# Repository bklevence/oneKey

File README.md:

oneKey 2020
===========

Project Focus
-------------------
Developing a low-cost (<$2) and accessible derivative of the MaKey MaKey so that it can be sustainably deployed via workshops at various library branches.

The aim is to introduce youth in underserved/low-income communities to making hardware that they can then tinker/play/make with. It's adressing the question "Can I take this home?" and the inability for youth to use take projects using digital media tools such as the MaKey MaKey home.

In participating in this process we hope for them to take more ownership of their tools. We're also trying to adress wether or not the library and its participants can make their own tools for learning via desktop manufacturing and production methods.

So what is a MaKey MaKey?
-------------------
From Sparkfun's [*MaKey MaKey Documentation*](https://github.com/sparkfun/makeymakey):

*"Using the MaKey MaKey you can make anything into a key (get it?) just by connecting a few alligator clips. The MaKey MaKey is an invention kit that tricks your computer into thinking that almost anything is a keyboard. This allows you to hook up all kinds of fun things as an input."*

**How does it work?**

*"The MaKey MaKey uses high resistance switching to detect when you've made a connection even through materials that aren't very conductive (like leaves, pasta or people). This technique attracts noise on the input, so a moving window averager is used to lowpass the noise. The on-board ATMega32u4 communicates with your computer using the Human Interface Device (HID) protocol which means that it can act like a keyboard or mouse."*

Methods
-------------------
The original oneKey uses a vinyl cutter and 3M copper tape to make a low-barrier and low-cost method for creating traces to solder onto. If working indoors take precautions with ventilalation etc. Working currently on a PCB kit version.

Need for the oneKey
-------------------
* 3M Copper Tape (used to be much cheaper, working on a thinner tape iteration.) ([Buy](http://www.amazon.com/inch-yds-Copper-Foil-Tape/dp/B00CBPM9RY/ref=sr_1_2?ie=UTF8&qid=1429671129&sr=8-2&keywords=copper+tape+3%22) | [HowTo](http://www.kobakant.at/DIY/?p=1132))
* Attiny85 ([Buy](http://www.digikey.com/product-detail/en/0/ATTINY85-20PU-ND) | [HowTo](about:blank))
* Attiny85 Standoff/ IC DIP Socket([Buy](http://www.digikey.com/product-detail/en/0/ATTINY85-20PU-ND) | [HowTo](about:blank))
* Resistors: 2x [68 ohm](http://www.digikey.com/product-detail/en/0/S68HCT-ND) , 1x [1.5K](http://www.digikey.com/product-detail/en/0/S1.5KHCT-ND), 1x [1M ohm](http://www.digikey.com/product-detail/en/0/CF14JT1M00CT-ND).
* Zener Diode ([Buy](http://www.digikey.com/product-detail/en/0/1N4148DICT-ND) | [HowTo](about:blank))
* USB Cable ([Buy](http://www.amazon.com/Eversame-Colorful-Hi-Speed-Universal-Phones-Black/dp/B00OC6WR22/ref=sr_1_1?s=pc&ie=UTF8&qid=1429671002&sr=1-1&keywords=10+pack+usb+cables) | [HowTo](about:blank))
* Vinyl Cutter (All makes/models work) ([Buy](http://www.amazon.com/Vinyl-Cutter-USCutter-34in-BUNDLE/dp/B00CDQGCTW/ref=sr_1_1?s=electronics&ie=UTF8&qid=1429671447&sr=1-1&keywords=vinyl+cutter) | [HowTo](about:blank))
* Soldering Iron ([Buy](about:blank) | [HowTo](about:blank))
* Needle Nose Pliers ([Buy](about:blank) | [HowTo](about:blank))
* Wire Cutter ([Buy](about:blank) | [HowTo](about:blank))
* Wire Stripper ([Buy](about:blank) | [HowTo](about:blank))
* Tiny AVR Programmer or Equivalent ([Buy](https://www.sparkfun.com/products/11801) | [HowTo](https://learn.sparkfun.com/tutorials/tiny-avr-programmer-hookup-guide/))

Repository Contents
-------------------
* **/Firmware** - Arduino Files+
* **/Hardware** - All design files (EAGLE, FRITIZING, AI+)
* **/Instructon** - Instructors materials
* **/Supplies** - Previous part orders

Variations
----------------
**Vinyl Cut Copper Tape**

This build requres soldering and takes an hour to construct. The tape can be tricky to adhere to a substrate, but for all intents and purposes IT WORKS!

Requires the installation of the Digispark Arduino IDE to upload and run code from /Firmware.
All vector files needed for vinylcutting reside in /Hardware.

**PCB(REV.1)**  

Looking to make a PCB kit, currently waiting for PCB to be milled. See the Eagle Schematics and Board files in /Hardware.

**Quick-build(Still in Development)**  
This build is solderless, can be built in less than an hour.

Links/Sources
-------------------
* [Digispark](http://digistump.com/products/1)
* [Digispark IDE](about:blank)
* [Digispark Clone](about:blank)
* [BhavyaShukla - Makey-makey-using-arduino-uno-r3-Multiple-input](https://github.com/BhavyaShukla/Makey-makey-using-arduino-uno-r3-Multiple-inputs-)
* [Moving Avarage Library](https://github.com/BhavyaShukla/Makey-makey-using-arduino-uno-r3-Multiple-inputs-)
* [JoyLab's/Sparkfun's - MaKey MaKey](https://github.com/sparkfun/makeymakey)
* [avrdude tutorials](https://learn.adafruit.com/usbtinyisp/avrdude)

toDo
-------------------
* easier peeling
* solderless
* remove usb cable
* ~~thruhole prototype~~
* non-digispark
* attiny45?
* find other hardware thruhole prototype
* do outreach, find other ppl who want this

brief history
-------------------
To date two iterations of the one input MaKey MaKey derivative, "MaKey MaKey MaKey", or officially "oneKey" for short, have been deployed. The first generation proved that youth could make, hack, and play with their own hardware. After various form and material explorations as well as a circuit redesign it is currently in its second phase. The new design is easier to handle, the cost per unit has dropped from $7 to $1.30, it's quicker to make, and there is still much more to refine.

people
-------------------
* bk brandonklevence@gmail.com
* the Maker Jawn Initiative info@makerjawn.org

License Information
-------------------
The hardware is released under [Creative Commons Share-alike 3.0](http://creativecommons.org/licenses/by-sa/3.0/).  
All other code is open source hardware so please feel free to do anything you want with it;
you buy me a beer if you use this and we meet someday ([Beerware license](http://en.wikipedia.org/wiki/Beerware)).
Please support [Digispark](https://github.com/sparkfun/makeymakey) and [JoyLabs](https://github.com/sparkfun/makeymakey) and buy their products if you decide to remix. Without their creativity and ingenuity this project would never have happened.

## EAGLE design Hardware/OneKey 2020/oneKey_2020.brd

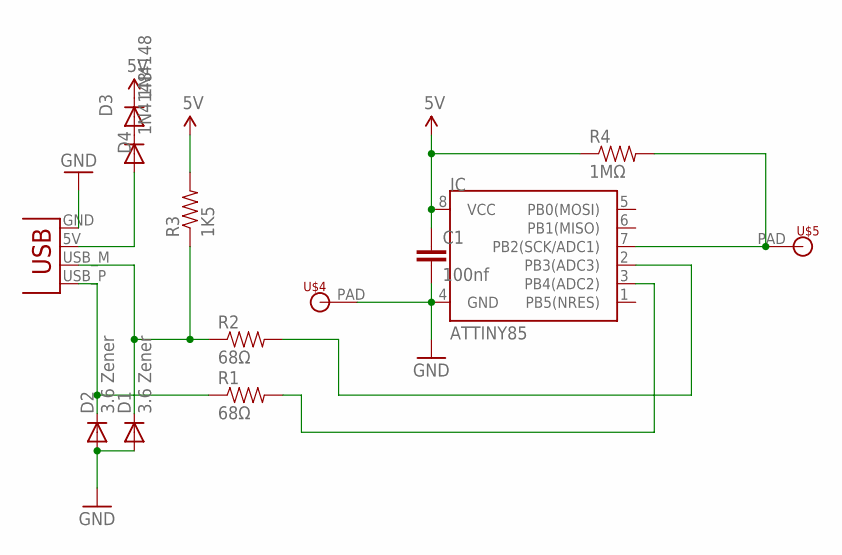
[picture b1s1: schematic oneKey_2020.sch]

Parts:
C1: 100nf; CAP-PTH-SMALL-KIT
D1, D2: 3.6 Zener; DO35-10
D3, D4: 1N4148; DO35-10
IC: ATTINY85; DIP08
R1, R2: 68Ω; AXIAL-0.3
R3: 1K5; AXIAL-0.3
R4: 1MΩ; AXIAL-0.3
U$4, U$5: MICROBIT_PAD
X1: USBPCB; USB-A-PCB

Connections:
5V: C1.1, D3.C, IC.8 (VCC), R3.P$2 (2), R4.P$1 (1)
GND: C1.2, D1.A, D2.A, IC.4 (GND), U$4.PAD, X1.GND
unnamed: IC.2 (PB3(ADC3)), R2.P$2 (2)
unnamed: IC.7 (PB2(SCK/ADC1)), R4.P$2 (2), U$5.PAD
unnamed: D3.A, D4.C
unnamed: D4.A, X1.5V (VBUS)
unnamed: IC.3 (PB4(ADC2)), R1.P$2 (2)
unnamed: D1.C, R2.P$1 (1), R3.P$1 (1), X1.USB_M (D-)
unnamed: D2.C, R1.P$1 (1), X1.USB_P (D+)

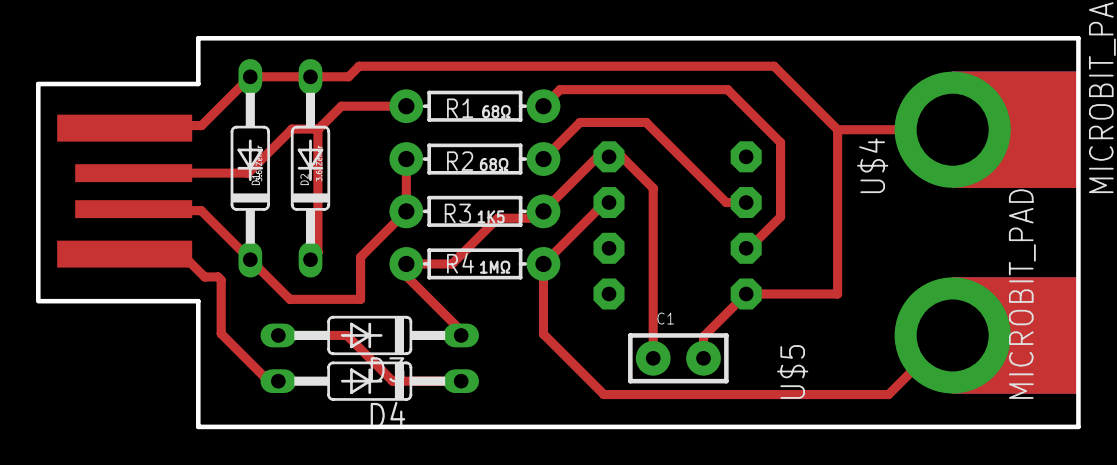
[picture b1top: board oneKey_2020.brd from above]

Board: 2 copper layers, 57.8 x 21.6 mm, 13 parts (1 on the bottom side), 9 nets.

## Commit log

2020-10-25 2020 Cleanup
2020-10-25 cleanup 2020
2020-10-25 2020 Board for Bantam Mill
    Added two extra zenner for WIN7 compatibility. Layout for Bantam Mill in eagle. Microbit-lik aligator pads replace old sparkfun makey makey design.
2021-04-12 cleanup

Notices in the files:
Hardware/OneKey 2020/oneKey_2020.brd:
Design (schematic, layout, concept) is licensed under the Creative Commons Attribution-ShareAlike 3.0 Unported License: http://creativecommons.org/licenses/by-sa/3.0
parts and their libraries:
SparkFun: Licensing: CC v3.0 Share-Alike You are welcome to use this library for commercial purposes.
